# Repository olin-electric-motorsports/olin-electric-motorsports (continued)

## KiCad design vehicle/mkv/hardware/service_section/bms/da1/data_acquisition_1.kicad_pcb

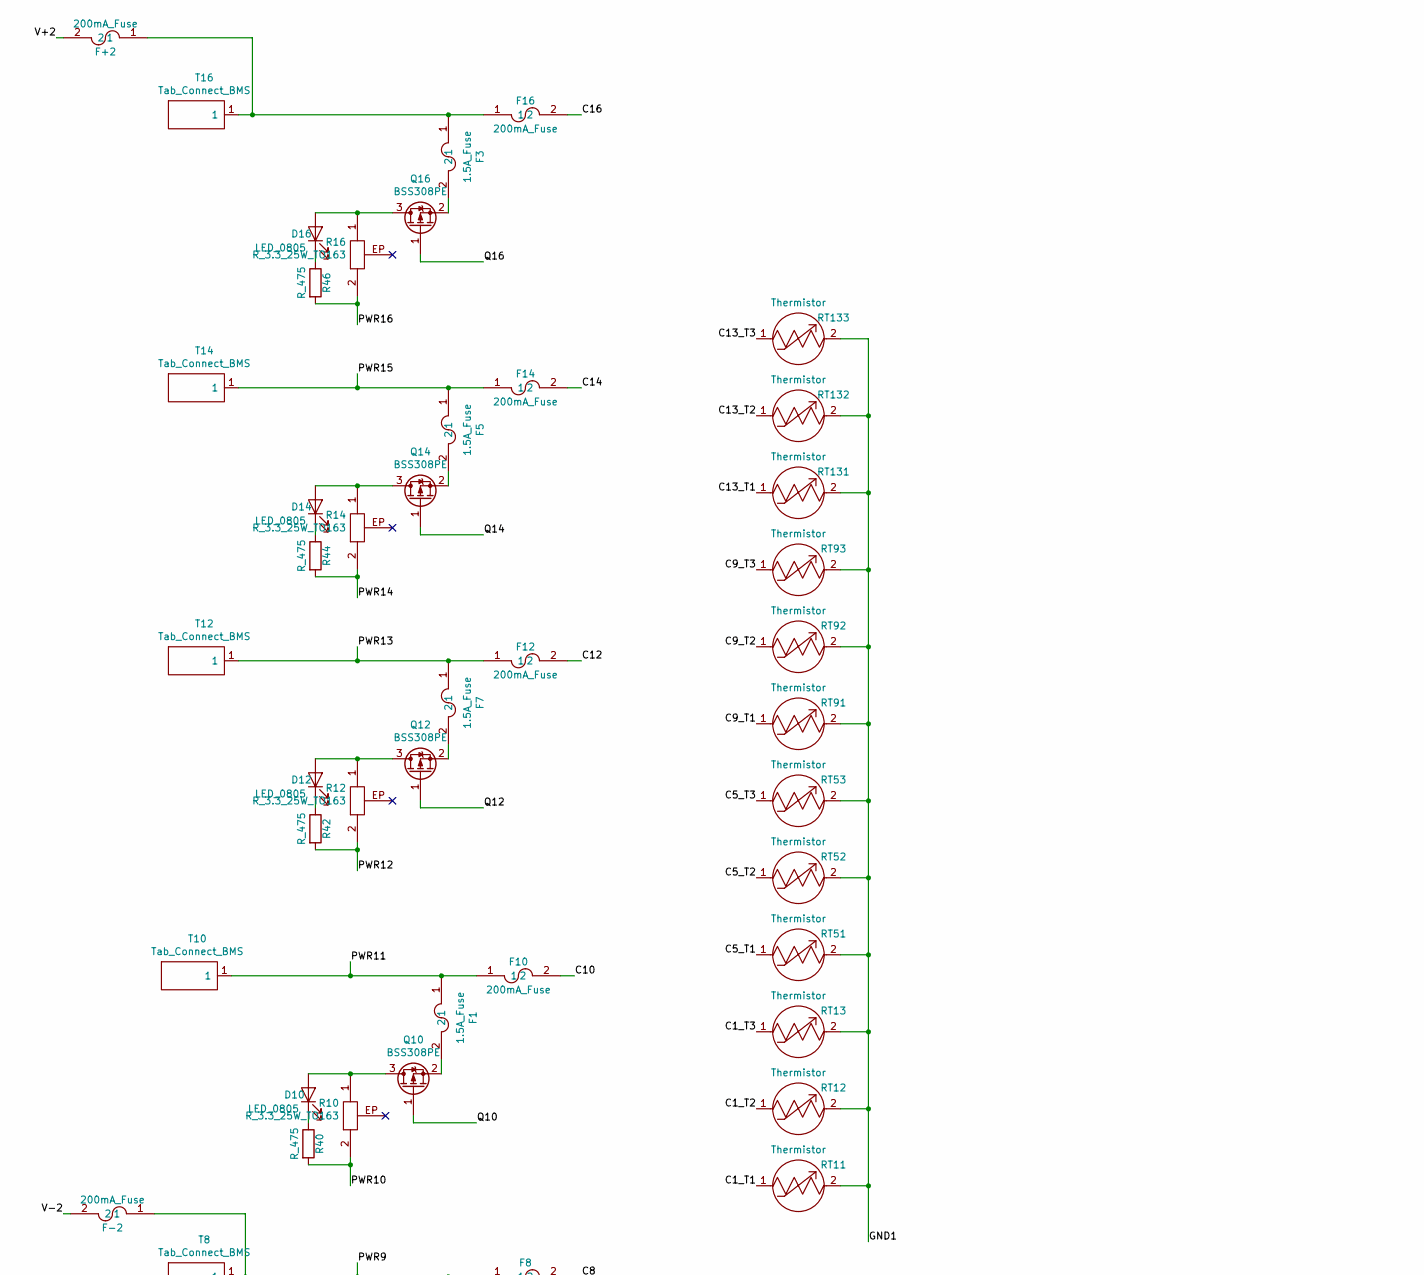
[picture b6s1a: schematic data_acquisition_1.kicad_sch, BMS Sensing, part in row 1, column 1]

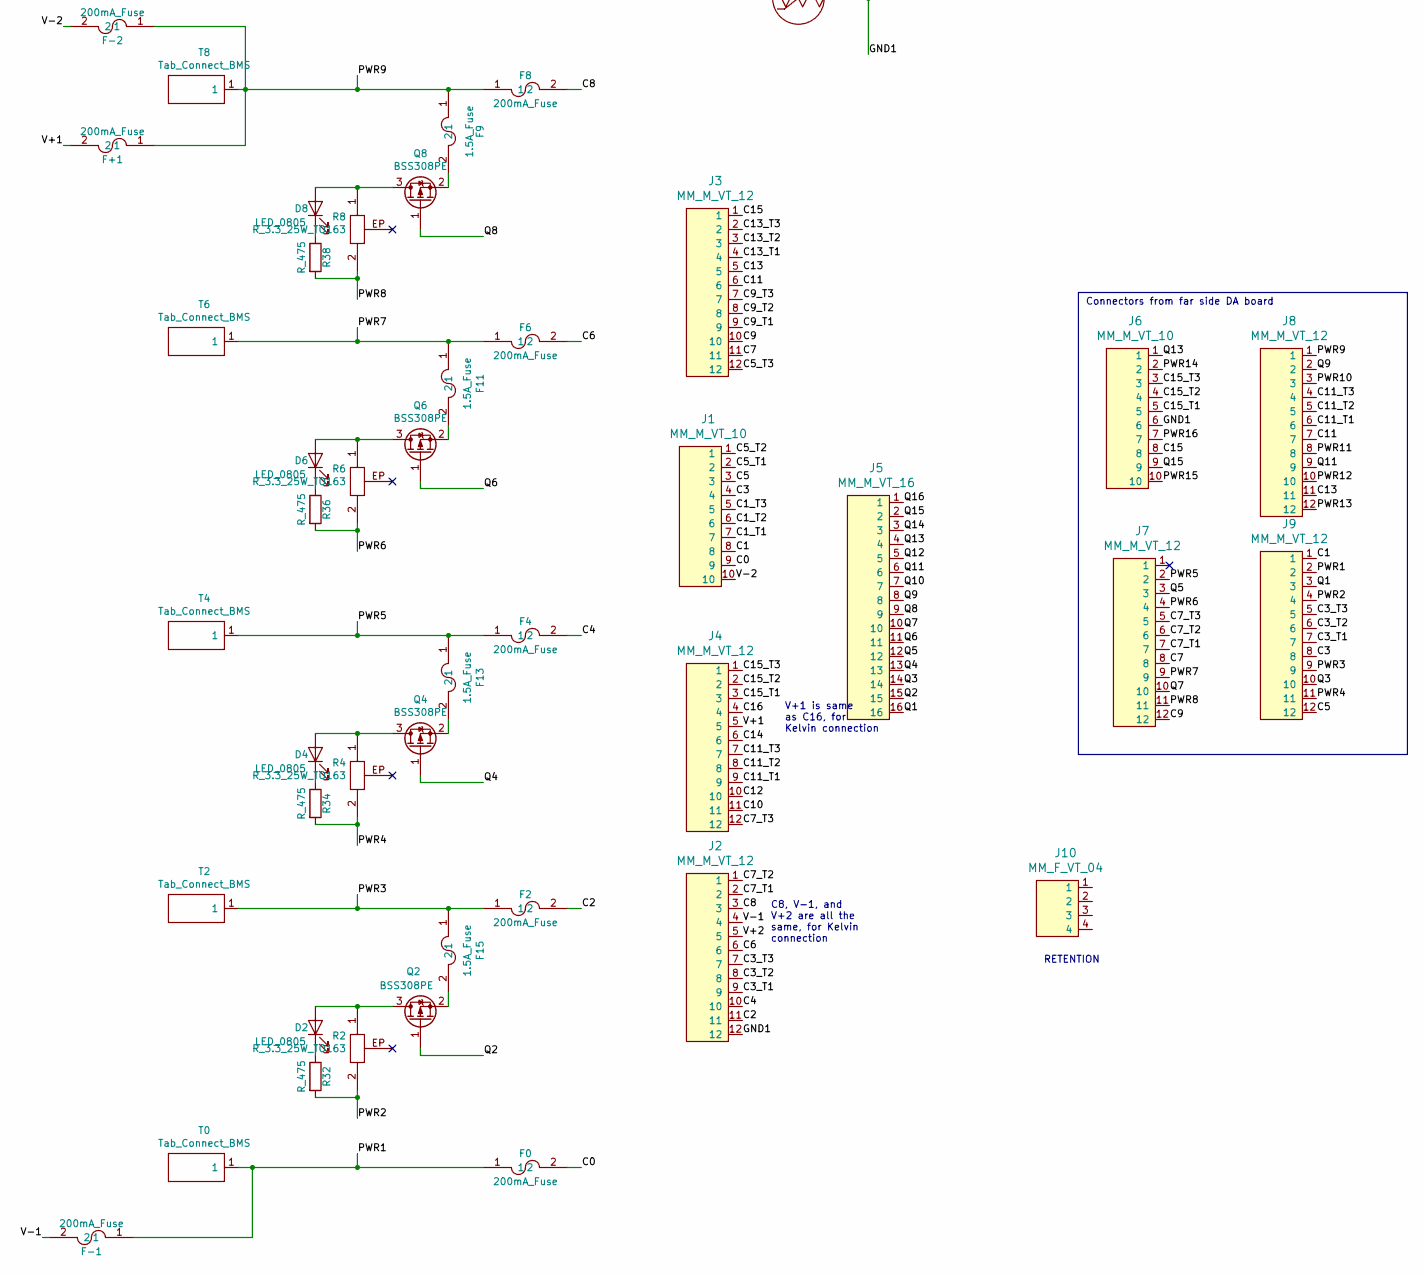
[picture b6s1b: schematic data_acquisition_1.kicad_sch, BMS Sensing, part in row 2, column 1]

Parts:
D2, D4, D6, D8, D10, D12, D14, D16: LED_0805; LED_0805_OEM; MPN 475-1410-1-ND
F0, F2, F4, F6, F8, F10, F12, F14, F16: 200mA_Fuse; Fuse_1812; MPN 507-1767-1-ND
F1, F3, F5, F7, F9, F11, F13, F15: 1.5A_Fuse; Fuse_1206; MPN F1462CT-ND
F+1, F+2: 200mA_Fuse; Fuse_1812; MPN 507-1767-1-ND
F-1, F-2: 200mA_Fuse; Fuse_1812; MPN 507-1767-1-ND
J1, J6: MM_M_VT_10; micromatch_female_vert_10; MPN 1-215464-0
J2, J3, J4, J7, J8, J9: MM_M_VT_12; micromatch_female_vt_12; MPN 1-215464-2
J5: MM_M_VT_16; micromatch_female_vert_16; MPN 1-215464-6
J10: MM_F_VT_04; micromatch_female_vert_4; MPN 338068-4
Q2, Q4, Q6, Q8, Q10, Q12, Q14, Q16: BSS308PE; SOT-23-3_OEM; MPN BSS308PEH6327XTSA1CT-ND
R2, R4, R6, R8, R10, R12, R14, R16: R_3.3_25W_TO163; PWR163; MPN PWR163S-25-3R30F-ND
R32, R34, R36, R38, R40, R42, R44, R46: R_475; R_0805_OEM; MPN 311-475CRCT-ND
RT11, RT12, RT13, RT51, RT52, RT53, RT91, RT92, RT93, RT131, RT132, RT133: Thermistor
T0, T2, T4, T6, T8, T10, T12, T14, T16: Tab_Connect_BMS; Tab_connect_BMS

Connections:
/C0: F0.2, J1.9
/C1: J1.8, J9.1
/C1_T1: J1.7, RT11.1
/C1_T2: J1.6, RT12.1
/C1_T3: J1.5, RT13.1
/C2: F2.2, J2.11
/C3: J1.4, J9.8
/C3_T1: J2.9, J9.7
/C3_T2: J2.8, J9.6
/C3_T3: J2.7, J9.5
/C4: F4.2, J2.10
/C5: J1.3, J9.12
/C5_T1: J1.2, RT51.1
/C5_T2: J1.1, RT52.1
/C5_T3: J3.12, RT53.1
/C6: F6.2, J2.6
/C7: J3.11, J7.8
/C7_T1: J2.2, J7.7
/C7_T2: J2.1, J7.6
/C7_T3: J4.12, J7.5
/C8: F8.2, J2.3
/C9: J3.10, J7.12
/C9_T1: J3.9, RT91.1
/C9_T2: J3.8, RT92.1
/C9_T3: J3.7, RT93.1
/C10: F10.2, J4.11
/C11: J3.6, J8.7
/C11_T1: J4.9, J8.6
/C11_T2: J4.8, J8.5
/C11_T3: J4.7, J8.4
/C12: F12.2, J4.10
/C13: J3.5, J8.11
/C13_T1: J3.4, RT131.1
/C13_T2: J3.3, RT132.1
/C13_T3: J3.2, RT133.1
/C14: F14.2, J4.6
/C15: J3.1, J6.8
/C15_T1: J4.3, J6.5
/C15_T2: J4.2, J6.4
/C15_T3: J4.1, J6.3
/C16: F16.2, J4.4
/GND1: J2.12, J6.6, RT11.2, RT12.2, RT13.2, RT51.2, RT52.2, RT53.2, RT91.2, RT92.2, RT93.2, RT131.2, RT132.2, RT133.2
/PWR1: F0.1, F-1.1, J9.2, T0.1
/PWR2: J9.4, R2.2, R32.2
/PWR3: F2.1, F15.1, J9.9, T2.1
/PWR4: J9.11, R4.2, R34.2
/PWR5: F4.1, F13.1, J7.2, T4.1
/PWR6: J7.4, R6.2, R36.2
/PWR7: F6.1, F11.1, J7.9, T6.1
/PWR8: J7.11, R8.2, R38.2
/PWR9: F8.1, F9.1, F+1.1, F-2.1, J8.1, T8.1
/PWR10: J8.3, R10.2, R40.2
/PWR11: F1.1, F10.1, J8.8, T10.1
/PWR12: J8.10, R12.2, R42.2
/PWR13: F7.1, F12.1, J8.12, T12.1
/PWR14: J6.2, R14.2, R44.2
/PWR15: F5.1, F14.1, J6.10, T14.1
/PWR16: J6.7, R16.2, R46.2
/Q1: J5.16, J9.3
/Q2: J5.15, Q2.1 (G)
/Q3: J5.14, J9.10
/Q4: J5.13, Q4.1 (G)
/Q5: J5.12, J7.3
/Q6: J5.11, Q6.1 (G)
/Q7: J5.10, J7.10
/Q8: J5.9, Q8.1 (G)
/Q9: J5.8, J8.2
/Q10: J5.7, Q10.1 (G)
/Q11: J5.6, J8.9
/Q12: J5.5, Q12.1 (G)
/Q13: J5.4, J6.1
/Q14: J5.3, Q14.1 (G)
/Q15: J5.2, J6.9
/Q16: J5.1, Q16.1 (G)
/V+1: F+1.2, J4.5
/V+2: F+2.2, J2.5
/V-1: F-1.2, J2.4
/V-2: F-2.2, J1.10
unnamed: D2.1 (K), R32.1
unnamed: D2.2 (A), Q2.3 (D), R2.1
unnamed: D4.1 (K), R34.1
unnamed: D4.2 (A), Q4.3 (D), R4.1
unnamed: D6.1 (K), R36.1
unnamed: D6.2 (A), Q6.3 (D), R6.1
unnamed: D8.1 (K), R38.1
unnamed: D8.2 (A), Q8.3 (D), R8.1
unnamed: D10.1 (K), R40.1
unnamed: D10.2 (A), Q10.3 (D), R10.1
unnamed: D12.1 (K), R42.1
unnamed: D12.2 (A), Q12.3 (D), R12.1
unnamed: D14.1 (K), R44.1
unnamed: D14.2 (A), Q14.3 (D), R14.1
unnamed: D16.1 (K), R46.1
unnamed: D16.2 (A), Q16.3 (D), R16.1
unnamed: F1.2, Q10.2 (S)
unnamed: F3.2, Q16.2 (S)
unnamed: F5.2, Q14.2 (S)
unnamed: F7.2, Q12.2 (S)
unnamed: F9.2, Q8.2 (S)
unnamed: F11.2, Q6.2 (S)
unnamed: F13.2, Q4.2 (S)
unnamed: F15.2, Q2.2 (S)
unnamed: F3.1, F16.1, F+2.1, T16.1

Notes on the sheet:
RETENTION
C8, V-1, and V+2 are all the same, for Kelvin connection
V+1 is same as C16, for Kelvin connection
Connectors from far side DA board

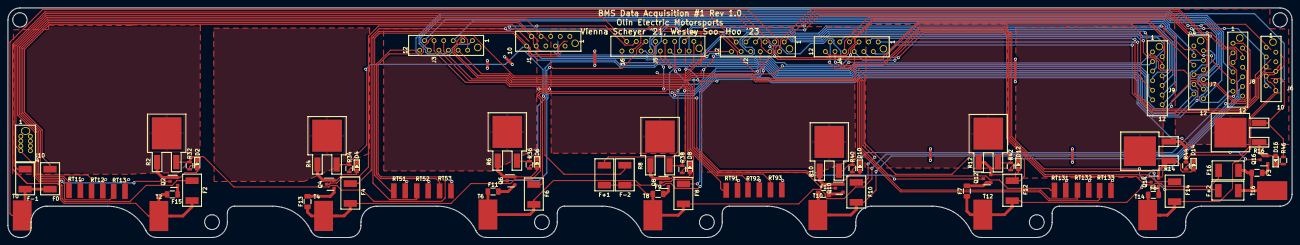
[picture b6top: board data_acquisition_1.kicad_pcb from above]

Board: 2 copper layers, 340.1 x 60.8 mm, 85 parts (1 on the bottom side), 103 nets.

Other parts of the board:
J8#2: MM_F_VT_04; micromatch_female_vert_4

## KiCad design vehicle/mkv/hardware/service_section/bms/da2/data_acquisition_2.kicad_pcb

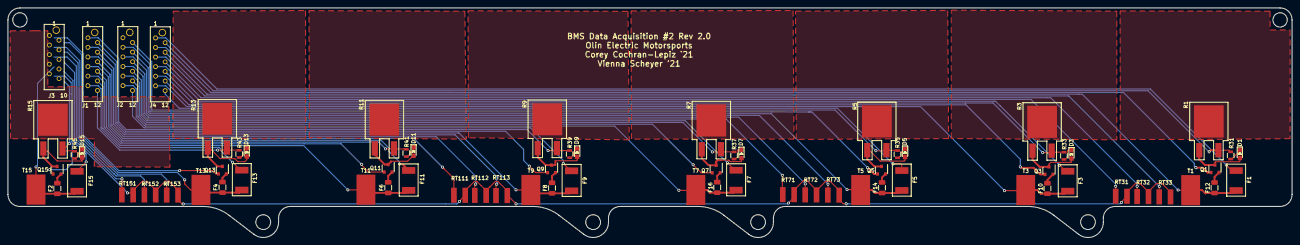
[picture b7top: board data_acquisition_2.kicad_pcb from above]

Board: 2 copper layers, 340.1 x 60.8 mm, 72 parts (0 on the bottom side), 69 nets.

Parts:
D1, D3, D5, D7, D9, D11, D13, D15: LED_0805; LED_0805_OEM
F1, F3, F5, F7, F9, F11, F13, F15: 200mA_Fuse; Fuse_1812
F2, F4, F6, F8, F10, F12, F14, F16: 1.5A_Fuse; Fuse_1206
J1, J2, J4: MM_M_VT_12; micromatch_female_vt_12
J3: MM_M_VT_10; micromatch_female_vert_10
Q1, Q3, Q5, Q7, Q9, Q11, Q13, Q15: BSS308PE; SOT-23-3_OEM
R1, R3, R5, R7, R9, R11, R13, R15: R_3.3_25W_TO163; PWR163
R31, R33, R35, R37, R39, R41, R43, R45: R_475; R_0805_OEM
RT31, RT32, RT33, RT71, RT72, RT73, RT111, RT112, RT113, RT151, RT152, RT153: Thermistor
T1, T3, T5, T7, T9, T11, T13, T15: Tab_Connect_BMS; Tab_connect_BMS

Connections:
/C1: F1.2, J4.1
/C3: F3.2, J4.8
/C3_T1: J4.7, RT31.1
/C3_T2: J4.6, RT32.1
/C3_T3: J4.5, RT33.1
/C5: F5.2, J4.12
/C7: F7.2, J2.8
/C7_T1: J2.7, RT71.1
/C7_T2: J2.6, RT72.1
/C7_T3: J2.5, RT73.1
/C9: F9.2, J2.12
/C11: F11.2, J1.7
/C11_T1: J1.6, RT111.1
/C11_T2: J1.5, RT112.1
/C11_T3: J1.4, RT113.1
/C13: F13.2, J1.11
/C15: F15.2, J3.8
/C15_T1: J3.5, RT151.1
/C15_T2: J3.4, RT152.1
/C15_T3: J3.3, RT153.1
/GND1: J3.6, RT31.2, RT32.2, RT33.2, RT71.2, RT72.2, RT73.2, RT111.2, RT112.2, RT113.2, RT151.2, RT152.2, RT153.2
/PWR1: J4.2, R1.2, R31.2
/PWR2: F1.1, F12.1, J4.4, T1.1
/PWR3: J4.9, R3.2, R33.2
/PWR4: F3.1, F10.1, J4.11, T3.1
/PWR5: J2.2, R5.2, R35.2
/PWR6: F5.1, F14.1, J2.4, T5.1
/PWR7: J2.9, R7.2, R37.2
/PWR8: F7.1, F16.1, J2.11, T7.1
/PWR9: J1.1, R9.2, R39.2
/PWR10: F8.1, F9.1, J1.3, T9.1
/PWR11: J1.8, R11.2, R41.2
/PWR12: F6.1, F11.1, J1.10, T11.1
/PWR13: J1.12, R13.2, R43.2
/PWR14: F4.1, F13.1, J3.2, T13.1
/PWR15: J3.10, R15.2, R45.2
/PWR16: F2.1, F15.1, J3.7, T15.1
/Q1: J4.3, Q1.1
/Q3: J4.10, Q3.1
/Q5: J2.3, Q5.1
/Q7: J2.10, Q7.1
/Q9: J1.2, Q9.1
/Q11: J1.9, Q11.1
/Q13: J3.1, Q13.1
/Q15: J3.9, Q15.1
unnamed: D1.1, R31.1
unnamed: D1.2, Q1.3, R1.1
unnamed: D3.1, R33.1
unnamed: D3.2, Q3.3, R3.1
unnamed: D5.1, R35.1
unnamed: D5.2, Q5.3, R5.1
unnamed: D7.1, R37.1
unnamed: D7.2, Q7.3, R7.1
unnamed: D9.1, R39.1
unnamed: D9.2, Q9.3, R9.1
unnamed: D11.1, R41.1
unnamed: D11.2, Q11.3, R11.1
unnamed: D13.1, R43.1
unnamed: D13.2, Q13.3, R13.1
unnamed: D15.1, R45.1
unnamed: D15.2, Q15.3, R15.1
unnamed: F2.2, Q15.2
unnamed: F4.2, Q13.2
unnamed: F6.2, Q11.2
unnamed: F8.2, Q9.2
unnamed: F10.2, Q3.2
unnamed: F12.2, Q1.2
unnamed: F14.2, Q5.2
unnamed: F16.2, Q7.2
